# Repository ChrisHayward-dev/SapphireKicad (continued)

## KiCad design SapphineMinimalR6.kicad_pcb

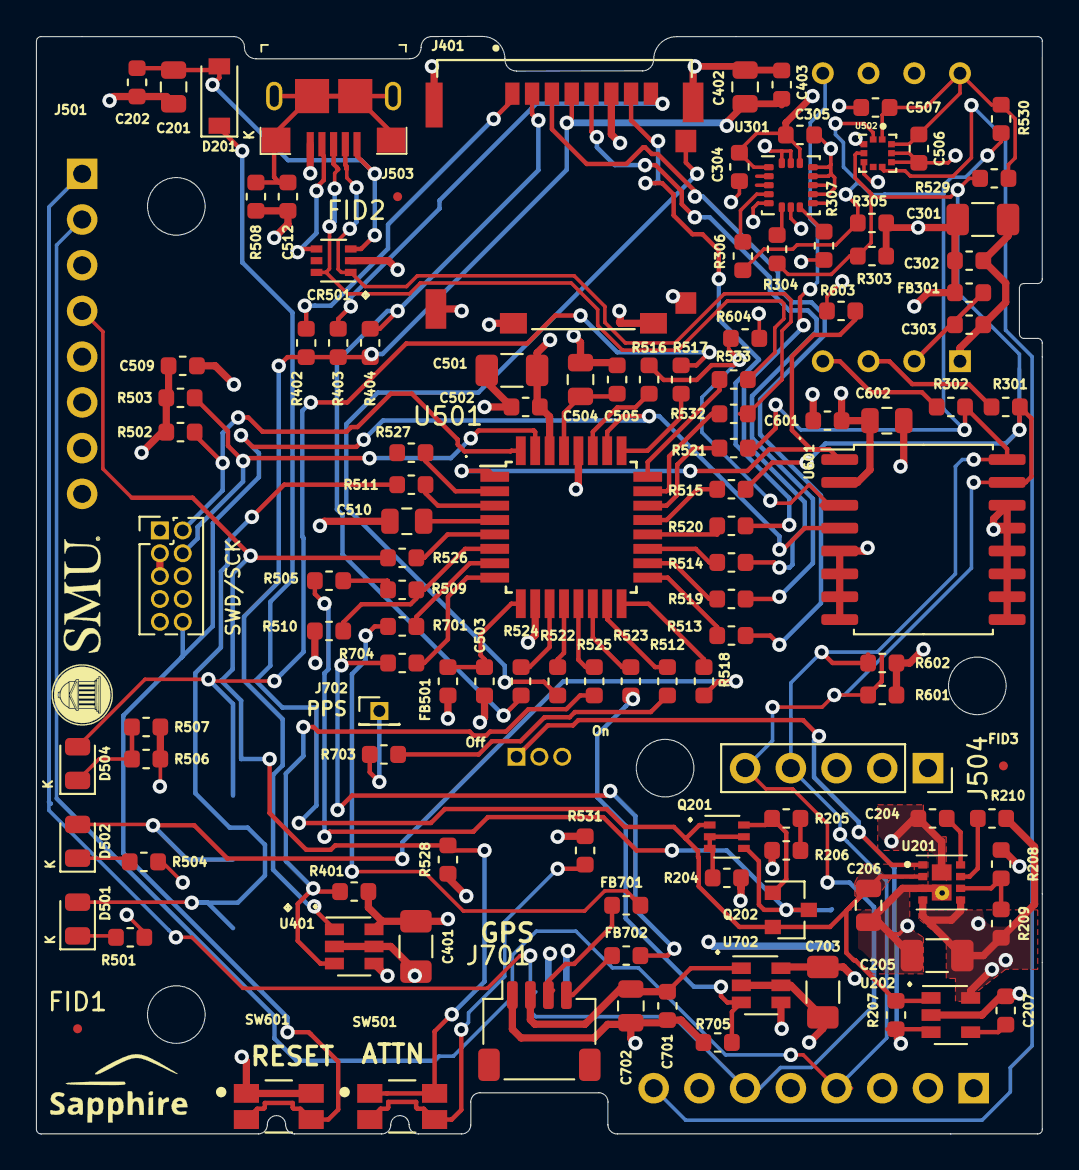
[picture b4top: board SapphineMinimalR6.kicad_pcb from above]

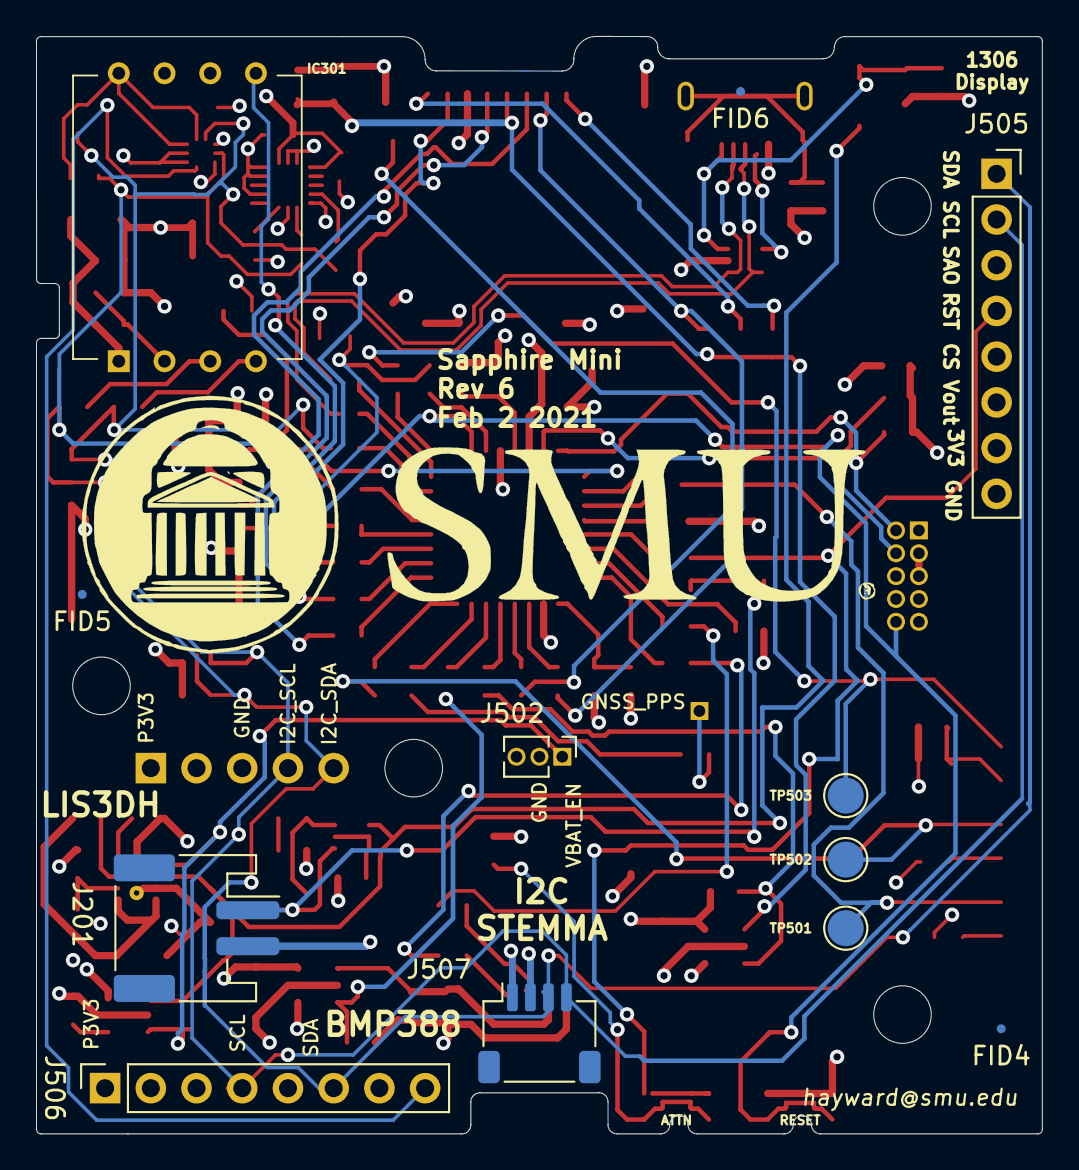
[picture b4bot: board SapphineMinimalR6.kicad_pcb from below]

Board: 4 copper layers, 55.9 x 61.0 mm, 130 parts (12 on the bottom side), 83 nets.

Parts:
C201, C206: 10uF; C_0805_2012Metric
C202, C207, C302, C303, C304, C305, C403, C502, C503, C505, C506, C507, C509, C512, C601, C701: 100nF; C_0603_1608Metric
C204: 560pF; C_0603_1608Metric
C205, C301, C401, C501, C703: 22uF; C_1206_3216Metric
C402, C504, C510, C602, C702: 1uF; C_0805_2012Metric
CR501: TPD4E1U06DCKR; SOT-363_SC-70-6
D201: MBR180; D_SOD-123
D501, D502: RED LED; LED_0805_2012Metric
D504: GREEN LED; LED_0805_2012Metric
FB301, FB501, FB701, FB702: 600; R_0603_1608Metric
FID1, FID2, FID3, FID4, FID5, FID6: Fiducial_0.5mm_Mask1mm
IC301: DLHR-F50D-E1BD-C-NAV8; DLHRF50DE1BDCNAV8
J201: JST; JST_PH_S2B-PH-SM4-TB_1x02-1MP_P2.00mm_Horizontal
J401: 503182-1852; MOLEX_503182-1852
J501: Conn_02x05_Odd_Even; PinHeader_2x05_P1.27mm_Vertical
J502: Conn_01x03_Male; PinHeader_1x03_P1.27mm_Vertical
J503: USB_B_Micro; USB_Micro_B_Female_10118193-0001LF
J504: Conn_01x05_Female; PinSocket_1x05_P2.54mm_Vertical
J505, J506: Conn_01x08_Female; PinSocket_1x08_P2.54mm_Vertical
J507, J701: Conn_01x04_Male; JST_SH_SM04B-SRSS-TB_1x04-1MP_P1.00mm_Horizontal
J702: Conn_01x01_Male; PinHeader_1x01_P1.27mm_Vertical
Q201: BC857BS; SOT-363_SC-70-6
Q202: IRLML6402TRPBF; SOT-23
R204, R205, R207, R208, R210, R401, R402, R403, R505, R509, R705: 100K; R_0603_1608Metric
R206, R404, R502, R503, R510, R528, R603, R604: 47K5; R_0603_1608Metric
R209: 309K; R_0603_1608Metric
R301, R302, R304, R306, R511, R512, R513, R515, R516, R517, R518, R519, R520, R521, R523, R524, R525, R526, R527, R532, R533, R701, R703, R704: 47; R_0603_1608Metric
R303, R305, R307: 10K; R_0603_1608Metric
R501, R504, R506, R507, R514, R522, R531: 2K; R_0603_1608Metric
R508, R529, R530, R601, R602: 4K75; R_0603_1608Metric
SW501: SW_Push_Dual; SW_EVQ-P7J01P
SW601: SW_Push_Dual_EVQ-P7J01P; SW_EVQ-P7J01P
TP501, TP502, TP503: TestPoint; TestPoint_Pad_D2.0mm
U201: TPS82150; TPS82130SILT
U202: SPX3819M5-L-3-3; SOT-23-5
U301: LIS3DH; LGA-16_3x3mm_P0.5mm_LayoutBorder3x5y
U401, U702: TPS22929D; SOT-23-6
U501: ATSAMD21E18A-AUT; TQFP-32_7x7mm_P0.8mm
U502: BMP388; PQFN50P200X200X80-10N
U601: DS3231SN; SOIC-16W_7.5x10.3mm_P1.27mm

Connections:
/P3V3: C205.1, C301.1, C302.1, C304.1, C305.1, C401.1, C501.1, C502.1, C506.1, C507.1, C509.1, C601.1, C602.1, C703.1, FB301.2, FB501.2, IC301.8, J501.1, J504.1, J505.7, J506.1, J507.2, R209.2, R210.1, R303.2, R305.2, R307.2, R401.1, R502.2, R503.2, R529.1, R530.1, R531.1, R601.1, R602.1, R603.1, R604.1, U201.4, U201.5, U202.5, U301.1, U301.14, U401.4, U401.6, U501.30, U502.1, U502.10, U601.2, U702.4, U702.6
/SapphireMini_DLHR/DLHR_EOC: IC301.5, R514.2
/SapphireMini_DLHR/I2C_SCL: J504.4, J505.2, J506.4, J507.4, R302.2, R303.1, R304.2, R521.2, R530.2, R602.2, U502.2, U601.16
/SapphireMini_DLHR/I2C_SDA: J504.5, J505.1, J506.6, J507.3, R301.2, R305.1, R306.2, R515.2, R529.2, R601.2, U502.4, U601.15
/SapphireMini_DS3231/32KHz: R603.2, U501.1, U601.1
/SapphireMini_DS3231/RESET: J501.10, SW601.1_2, SW601.2_2, U501.26, U601.4
/SapphireMini_GNSS/GNSS_PWR: R523.2, R705.2, U702.3
/SapphireMini_GNSS/RS232_RXD: R701.2, U501.7
/SapphireMini_GNSS/TIMEMARK: R512.2, R703.1
/SapphireMini_Power/PWR_IN: C206.1, D201.1, Q201.1, Q202.2, R207.2, U201.2, U202.1
/SapphireMini_Power/VBAT: J201.1, Q201.4, Q202.3, R505.1
/SapphireMini_Power/VBAT_EN: J502.1, R207.1, U201.1, U202.3
/SapphireMini_Proc/1306RST: J505.4, R526.2, R528.1, SW501.1_1, SW501.2_1
/SapphireMini_Proc/AREF: C510.1, U501.4
/SapphireMini_Proc/BMP_INT: J506.8, U502.7
/SapphireMini_Proc/D+: CR501.6, J503.3, R533.2
/SapphireMini_Proc/D-: CR501.1, J503.2, R532.2
/SapphireMini_Proc/GREEN_LED: D504.2, R517.2, TP503.1
/SapphireMini_Proc/LOCAL_PPS: R516.2, R604.2, U601.3
/SapphireMini_Proc/RED_LED: D501.2, R511.2, TP501.1
/SapphireMini_Proc/RED_LED2: D502.2, R518.2, TP502.1
/SapphireMini_Proc/RS232_RXD5: R704.1, U501.8
/SapphireMini_Proc/SD_CD: J401.SW, R522.2
/SapphireMini_Proc/SD_CS: J401.2, R404.2, R524.2
/SapphireMini_Proc/SD_PWR: R401.2, R525.2, U401.3
/SapphireMini_Proc/SPI_MISO: J401.7, R520.2
/SapphireMini_Proc/SPI_MOSI: J401.3, R513.2
/SapphireMini_Proc/SPI_SCK: J401.5, R519.2
/SapphireMini_Proc/SWCLK: J501.4, R503.1, U501.31
/SapphireMini_Proc/SWDIO: J501.2, R502.1, U501.32
/SapphireMini_Proc/VBAT_MON: R509.2, R510.1, U501.6
/SapphireMini_Proc/VBUS: C201.1, C202.1, CR501.3, D201.2, J503.1
GND: C201.2, C202.2, C204.2, C205.2, C206.2, C207.2, C301.2, C302.2, C303.2, C304.2, C305.2, C401.2, C402.2, C403.2, C501.2, C502.2, C503.2, C504.2, C505.2, C506.2, C507.2, C509.2, C510.2, C512.2, C601.2, C602.2, C701.2, C702.2, C703.2, CR501.2, IC301.1, J201.2, J401.6, J401.DT, J401.P1, J401.P2, J401.P3, J401.P4, J401.P5, J501.3, J501.5, J501.9, J502.2, J503.5, J504.3, J505.8, J506.3, J507.1, J701.4, R204.2, R206.2, R208.1, R501.2, R504.2, R506.2, R507.2, R508.1, R510.2, R528.2, R705.1, SW601.1_1, SW601.2_1, U201.3, U201.9, U202.2, U301.5, U301.7, U301.10, U301.12, U301.13, U301.15, U301.16, U401.2, U401.5, U501.10, U501.28, U502.3, U502.5, U502.8, U502.9, U601.5, U601.6, U601.7, U601.8, U601.9, U601.10, U601.11, U601.12, U601.13, U601.14, U702.2, U702.5
unnamed: C204.1, U201.8
unnamed: C207.1, U202.4
unnamed: C303.1, FB301.1, IC301.2
unnamed: C402.1, C403.1, J401.4, R402.2, R403.1, R404.1, U401.1
unnamed: C503.1, FB501.1, U501.9
unnamed: C504.1, C505.1, U501.29
unnamed: C512.1, J503.6, R508.2
unnamed: C701.1, C702.1, J701.1, U702.1
unnamed: CR501.4, J503.4
unnamed: D501.1, R501.1
unnamed: D502.1, R504.1
unnamed: D504.1, R506.1, R507.1
unnamed: FB701.1, J701.2
unnamed: FB701.2, R701.1
unnamed: FB702.1, R704.2
unnamed: FB702.2, J701.3
unnamed: IC301.3, R301.1
unnamed: IC301.4, R302.1
unnamed: J401.1, R402.1
unnamed: J401.8, R403.2
unnamed: J702.1, R703.2
unnamed: Q201.2, Q201.3, Q201.5, R204.1
unnamed: Q201.6, Q202.1, R205.1
unnamed: R205.2, R206.1
unnamed: R208.2, R209.1, U201.6
unnamed: R210.2, U201.7
unnamed: R304.1, U301.4
unnamed: R306.1, U301.6
unnamed: R307.1, U301.8
unnamed: R505.2, R509.1
unnamed: R511.1, U501.3
unnamed: R512.1, U501.15
unnamed: R513.1, U501.17
unnamed: R514.1, U501.19
unnamed: R515.1, U501.21
unnamed: R516.1, U501.27
unnamed: R517.1, U501.25
unnamed: R518.1, U501.16
unnamed: R519.1, U501.18
unnamed: R520.1, U501.20
unnamed: R521.1, U501.22
unnamed: R522.1, U501.12
unnamed: R523.1, U501.14
unnamed: R524.1, U501.11
unnamed: R525.1, U501.13
unnamed: R526.1, U501.5
unnamed: R527.1, U501.2
unnamed: R531.2, SW501.1_2, SW501.2_2
unnamed: R532.1, U501.23
unnamed: R533.1, U501.24

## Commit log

2022-09-22 Initial Commit from first 100 production
2022-09-25 From RA_Old Modified"
2022-09-26 end of day
2022-09-26 3d references'
2022-09-26 Corrected to get clean review on schematic
2022-09-27 Minor changes to annotation
2022-09-28 daily update
2022-09-28 Footprints complete. Starting layout
2022-09-29 replacing w/ resistor array
2022-09-29 Working on update to power controllers
2022-10-01 Checkpoint
2022-10-03 Fully routed. Needs DRC check and cleanup
2022-10-03 Clean PCB but Added new clock to schematic
2022-10-04 Updating for parts avail
2022-10-10 snapshot
2022-10-13 Delete SapphineMinimal-2022-10-05_152435.zip
    to fix
2022-10-13 Skematic updated for power and 1PSI sensor
2022-10-15 Start of layout
2022-10-16 Completed board Rev 1
2022-10-17 updated new layout - no routing
2022-10-18 backup
2022-10-24 6 Layer Routing
2022-10-25 special redo
2022-10-25 Copper Routed
2022-10-26 Added optional RSCK footprint
2022-10-26 Fixing board problems
2022-10-27 Updated clean pcb
2022-10-28 updates to power plane
2022-10-28 Release to OSH Park
2022-10-28 OSH Park Release1
2022-10-28 Updates for Circuit Hub estimates
2023-01-30 Updated PCB comments
2023-02-19 M2 with notes before board updates
2023-02-19 Updated to fix noted problems
2023-02-20 InProgress
2023-02-20 M2R2 basic DRC passed
2023-02-21 Setup for handsolder, 6 layers
2023-02-21 4 Layer Hand Solder version
2023-02-21 Sapphire M2R2 submitted to OSH Park 2/21/2023
2023-02-22 HTML assembly bom created
2023-03-04 Design R2 sent to OSH Park
2023-03-06 End of Weekend
2023-03-06 Partial Routing
2023-03-07 Clean DRC
2023-03-07 Midst of pretying layout
2023-03-08 Prior to handsolder footprints
2023-03-11 Added hand solder pads
2023-03-12 Added slot for wiring
2023-03-14 OSH_ParkM2R3
2023-04-23 Board Assembled w/ errors. Ready for redo
2023-05-02 Board ready for final check
2023-05-03 End of Day2
2023-05-03 OSH Park 5-3-2023
2023-06-07 Updated to correct wiring of IIM42351
2023-06-19 Updated for 32KHz input on IIM42351
2024-02-04 After M2 at home. Not sure what changes are
2025-09-10 Current KiCad from last production
